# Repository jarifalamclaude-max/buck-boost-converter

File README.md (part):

# SafeBuck-80 — 80 W protected buck-boost (LT8390 + LM74930)

**Banglay:** QS-1212CCBD (80 W automatic buck-boost) er moton ekta module (72 × 54 mm — QS-1212CCBD theke 7 × 6 mm boro, thanda thakar jonno), kintu
**4-switch synchronous buck-boost** (LT8390) diye — efficiency 93–97 % — ar **"smoke-tester" protection** shoho:
input ba output e vhul connection dile board purbe na, shudhu **red LED** jolbe. Puro design KiCad 7 e,
JLCPCB te sorasori order korar file shoho.

**English:** A 72 × 54 mm, 80 W, CV + CC buck-boost module, a little larger than the QS-1212CCBD (65 × 48 mm) for cooling. It uses a 4-switch
synchronous controller (LT8390) and full wrong-wiring protection: reversed input, over-voltage, under-voltage,
output short and a reversed battery on the output. Every one of these only lights a red LED.

| | |
|---|---|
| Input | 9–36 V (starts at 8.2 V, stops below 7.5 V), survives −60 V reversed and up to +60 V DC (cut-off above ~43 V, back on below ~39 V) |
| Output | 1.6–36 V (CV, 25-turn pot; the pot reaches ~39 V) and 0.94–8.33 A (CC, 25-turn pot), max 80 W |
| Topology | 4-switch synchronous buck-boost, 300 kHz ±15 % spread spectrum, peak-current mode |
| Efficiency (calculated) | 96.2–96.9 % (24 → 14.4 V, 80 W) · 93.4–94.8 % (9 → 35 V, 80 W) · 94.7–95.5 % (12 → 12 V) |
| Protection | reverse input to −60 V, OV cut-off ~43 V, UV 7.5 V, inrush limit, input short while running (Q1 gate clamp), output short (CC + 62.5 A instant trip), reversed battery on output (Q7 opens in 1–6 µs), battery above the CV setting (FB clamp), inductive loads (VOUT clamp diode), thermal foldback (PTC), last-resort fuses on both sides |
| Indicators | green = ON, red IN = input reversed / OV / UV, red OUT = battery reversed on the output |
| PCB | 72 × 54 mm (parts in a 65 × 48 mm area, the rest is GND copper for cooling), 2 layers, **2 oz copper**, 1.6 mm, all SMD on top (4 THT parts: 2 terminals, 2 pots), M3 holes in 3 corners |
| Board art | BRACU **Duburi** logo and "Designed by Jarif Alam" on the bottom silkscreen |

| Top (power stage + parts) | Bottom (GND plane, mirrored) |
|---|---|
|  |  |

> **Status / caveat:** the design is checked by calculation (`calc/design.py`: 57 checks, 56 pass, the one "fail" is the
> "bare-board rise above 45 °C at 80 W" note, now +46 °C), by netlist ↔ schematic ↔ PCB consistency checks (`hardware/verify.py`: all pass), by KiCad DRC
> (fully routed: 0 unconnected, 0 clearance, 0 dangling; the only DRC warnings are silkscreen overlaps and library-path notes) and by
> two rounds of independent review (the second round's 8 major findings are fixed or listed under Limitations). **It has not been built and measured yet.** Build one, follow the first-power-up steps in the build guide,
> and check the loop compensation with a load step before trusting it at 80 W.

---

## Documents (shuru korun ekhan theke)

| File | Ki ache |
|---|---|
| [`kicad/`](kicad/) | **KiCad project — open `kicad/SafeBuck-80.kicad_pro`** (schematic + routed PCB + project libraries). `kicad/SafeBuck-80_KiCad.zip` = same files in one download |
| [`docs/SafeBuck-80_Build_Guide.pdf`](docs/SafeBuck-80_Build_Guide.pdf) | **Noob-der jonno**: JLCPCB order step by step, first power-up, CV/CC set, protection test, troubleshooting |
| [`docs/SafeBuck-80_How_It_Works.pdf`](docs/SafeBuck-80_How_It_Works.pdf) | **Sohoj bhashay**: buck/boost kivabe kaj kore (chobi soho), component chena, board map + all 113 parts (ki kaj kore, value keno, na thakle ki hoto), fault table, design process. Source: `docs/make_how_it_works.py` |
| [`docs/SafeBuck-80_Component_Guide.pdf`](docs/SafeBuck-80_Component_Guide.pdf) | **Kon component keno**: every part's role, why it was chosen, full BOM with LCSC numbers |
| [`docs/SafeBuck-80_Schematic.pdf`](docs/SafeBuck-80_Schematic.pdf) | Full schematic (exported from KiCad) |
| [`docs/current_flow/index.html`](docs/current_flow/index.html) | **Current flow page**: 3D board, step-by-step current path (buck, boost, control, input ulta, output-e battery ulta, short), threshold-set-kora part-gulo formula shoho, shob part-er table. Folder download kore browser-e kholo (ba web server diye) |
| [`docs/layout-rules.md`](docs/layout-rules.md) | PCB layout rules used (hot loops, Kelvin sense, ground, thermal) |
| [`jlcpcb/ORDER_NOTES.md`](jlcpcb/ORDER_NOTES.md) | What to upload and which settings to pick at JLCPCB |

## JLCPCB te order (short version)

1. `jlcpcb/SafeBuck-80_gerbers.zip` upload. Settings: **2 layers, 1.6 mm, 2 oz outer copper**.
2. Turn on PCB Assembly (Standard, top side), then upload `jlcpcb/SafeBuck-80_BOM.csv` + `jlcpcb/SafeBuck-80_CPL.csv`.
3. Check the placement preview (pin-1 of U1/U2, FETs, diodes, LEDs, C11/C18 polarity) and order.
   Details are in [`jlcpcb/ORDER_NOTES.md`](jlcpcb/ORDER_NOTES.md).

## File chart — protita file ki kaj kore

| Path | Kaj (what it does) |
|---|---|
| `hardware/netlist.py` | **Single source of truth.** Every part: ref, value, footprint, MPN, LCSC number, role and pad → net map. Everything below is generated from this file |
| `hardware/placement.py` | Position/rotation of every part on the 72 × 54 mm board (hot-loop layout explained in the header) |
| `hardware/build_pcb.py` | Builds the custom LT8390 footprint, places all footprints, assigns nets, draws the outline, runs DRC → `kicad/SafeBuck-80_placed.kicad_pcb` |
| `hardware/route.py` | Power copper zones (union of rectangles, checked against foreign pads) → Specctra DSN (zones as fixed wires, net-tie keepouts) → Freerouting → imports the session → hand fan-out stubs at U2 → completion router → GND pours, stitching vias, GND pocket merge vias and hookups, dead-end cleanup, DRC → `kicad/SafeBuck-80.kicad_pcb` |
| `hardware/complete_routes.py` | Two-layer grid A* router (0.05 mm grid, 0.2 mm track, 0.205 mm gap) that finishes the connections Freerouting leaves open: rip-up with rollback, Kelvin net-tie entry, via keep-back at fine-pitch pins, string-pulled tracks |
| `hardware/make_schematic.py` | Generates the KiCad schematic `kicad/SafeBuck-80.kicad_sch` + project symbol library `SafeBuck.kicad_sym`; symbol UUIDs match the footprints |
| `hardware/make_jlcpcb.py` | Makes the JLCPCB package (Gerber + drill zip, BOM, CPL) |
| `hardware/make_logo.py` | Turns a logo image (`docs/img/duburi_logo.png`) into a silkscreen footprint for the board's bottom side; without an image it draws a "DUBURI" text badge |
| `hardware/verify.py` | One-command check: netlist ↔ schematic ↔ PCB, footprint links, DRC summary |
| `hardware/check_place.sh` | Quick placement check: build, list courtyard overlaps, SVG preview |
| `hardware/routing/SafeBuck-80_freerouting.ses` | The Freerouting session the routed board was built from (input of `route.py complete`) |
| `kicad/` | Copy of the KiCad project for opening/downloading (made by `make_jlcpcb.py`), plus a zip |
| `hardware/kicad/SafeBuck-80.kicad_pro` | KiCad project as generated by the scripts (same files as `kicad/`) |
| `hardware/kicad/SafeBuck-80.kicad_sch` | Schematic (label style: every pin has a net label) |
| `hardware/kicad/SafeBuck-80.kicad_pcb` | Routed 2-layer PCB |
| `hardware/kicad/SafeBuck.kicad_sym`, `SafeBuck.pretty/` | Project libraries: LT8390, LM74930, SOT-23 diode symbols; LT8390 FE28 footprint with 10 thermal vias |
| `hardware/kicad/sym-lib-table`, `fp-lib-table` | Point KiCad at the project libraries (loaded automatically) |
| `hardware/kicad/drc_routed.rpt` | KiCad DRC report of the routed board |
| `calc/design.py` | Every design equation from the datasheets: inductor, RSENSE, slope compensation, losses, ripple, UVLO/OV, inrush, LEDs, thermal, fault simulation of a reversed battery hit → `report.txt`, `results.json` |
| `calc/report.txt` | Human-readable result of all 57 checks |
| `docs/make_docs.py`, `docs/print_pdf.js`, `docs/src/*.html` | Build the PDF guides (edit the HTML, run the script) |
| `jlcpcb/` | Files to upload to JLCPCB |

Regenerate everything (Ubuntu with KiCad 7, Java, Node + Playwright):

```bash
cd hardware && python3 make_logo.py && /usr/bin/python3 build_pcb.py && /usr/bin/python3 route.py complete routing/SafeBuck-80_freerouting.ses && python3 make_schematic.py && /usr/bin/python3 verify.py && python3 make_jlcpcb.py && cd .. && python3 docs/make_docs.py
```

`routing/SafeBuck-80_freerouting.ses` is the Freerouting session this board was made from. `route.py route` runs
Freerouting from scratch instead; its result changes from run to run, so the completion step can end differently.

## Block diagram

```
J1 VIN+ ─ F1 15A ─┬─ D1 TVS        ┌──────── LT8390 4-switch buck-boost ────────┐
                  │                │  Q3 ┐            R15 3mΩ        ┌ Q6        │
                  └─ Q1 ─┬─ Q2 ──── VIN_P ─┤ SW1 ─[RSENSE]─ L1 10µH ─ SW2 ├─ VOUT_C ─ R31 12mΩ ─ F2 10A ─ J2 OUT+
             (HGATE)  CSRC (DGATE) │  Q4 ┘   (peak current)          └ Q5        │     (CC sense)
                     LM74930       └─────────────────────────────────────────────┘
             reverse/OV/UV, FLT→red IN                                    J2 OUT− ─ Q7 (100 V) ─ GND
                                                                 trips: Q9 (I>83 A), Q11 (OUT+<−1.85 V), hold: Q10, red OUT
```

## Fault matrix (vhul connection hole ki hoy)

| Wrong connection | What protects | Result |
|---|---|---|
| Input reversed (up to −60 V) | LM74930 + Q2 block, D1 is bidirectional | red IN LED, no current, nothing hot |
| Input 43–60 V DC | LM74930 OV opens Q1 (back on below 39.4 V; worst case ≥ 37.4 V, so a 36 V supply always restarts) | red IN LED, output off |
| Input shorted while running | D17 (15 V zener) clamps Q1's gate-source; Q2 blocks reverse current | output off, no damage |
| Input spike (hot-plug, cable inductance) | D1 SMBJ60CA, R1/C1 input RC damper, C11 ESR damping | clamped |
| Input below 7.5 V | LM74930 UV + LT8390 EN/UVLO | output off, red IN LED |
| Output short circuit | LT8390 CC limit (keep-running) + 62.5 A instant ISOC | runs at the CC current, recovers when the short is removed |
| Battery reversed on the output (≤ 35 V), any CV setting | Q9 (current > 83 A) or Q11 (OUT+ < −1.85 V) turns Q7 off within 1–6 µs, Q10 holds it off; D15 keeps VOUT_C above about −1.5 V | red OUT LED, peak 52–184 A for a few µs, Q7 avalanche ≤ 19 mJ (rated 274 mJ) |
| Battery (correct polarity) above the CV setting, e.g. 36 V battery at CV 1.6 V | R46 + D14 hold the FB pin below 5.4 V (6 V abs max); LT8390 stops switching (FB over-voltage) | no damage; the battery is not discharged when VIN is off |
| Inductive load (motor, solenoid) when the converter stops | D15 Schottky takes the freewheel current (OUT+ ≈ −1 V, Q11 trips only below −1.85 V) | no false trip, no avalanche |
| Battery on the output, correct polarity, input off | Q7 off without VIN | no drain (µA) |
| Overheating | PTC TH1 pulls CTRL down | current folds back at about 105 °C, stops at about 130 °C, auto-restarts |
| A MOSFET fails short | F1 / F2 | fuse opens (last resort only) |

**Never connect OUT− to VIN− outside the board (no common ground).** OUT− is switched by Q7. With a common ground the
converter still works, but (1) a battery reversed on the output is no longer blocked (F2 has to blow), and (2) if the
input is then also reversed, the supply is shorted through Q7's body diode. Use a floating load / separate supply,
which is how a bench "smoke tester" is normally wired.

## KiCad libraries used

| Library | Used for |
|---|---|
| `Device` (KiCad 7 standard) | R, C, C_Polarized, L, D, D_TVS, LED, Fuse, R_Potentiometer, Thermistor_PTC, Q_NPN_BEC, Q_PNP_BEC, NetTie_2 symbols |
| `Transistor_FET` | CSD18532Q5B, CSD19532Q5B symbols (TDSON-8 pinout: 1–3 S, 4 G, 5 D) |
| `Connector`, `Mechanical` | Screw_Terminal_01x02, TestPoint, MountingHole |
| `SafeBuck` (this project, `SafeBuck.kicad_sym`) | LT8390, LM74930, D_SOT23 (BAS21), DZ_SOT23 (BZX84) |
| Footprints: `Resistor_SMD`, `Capacitor_SMD`, `Diode_SMD`, `LED_SMD`, `Package_TO_SOT_SMD` (SOT-23, TDSON-8-1), `Package_DFN_QFN` (HVQFN-24 4×4), `Inductor_SMD` (L_Coilcraft_XAL1510-103), `Fuse` (Littelfuse NANO2 451/453), `Potentiometer_THT` (Bourns 3296W), `TerminalBlock_Phoenix` (MKDS 1,5/2-5,08), `TestPoint`, `MountingHole`, `NetTie` | Standard KiCad 7 footprints |
| `SafeBuck.pretty` (this project) | `LT8390_FE28_EB_TSSOP-28_EP4.75x2.74mm`: ADI FE28 (EB) land pattern with 2 × 5 thermal vias |

## Datasheets and sources I read

**Chosen parts**
- LT8390 (Analog Devices): https://www.analog.com/media/en/technical-documentation/data-sheets/LT8390.pdf
  (the copy I worked from was the public Chinese version hosted by LCSC: https://atta.szlcsc.com/upload/public/pdf/source/20221018/54D796C872281B2AD115D8A08B7AE0F6.pdf)
- LM74930-Q1 (TI): https://www.ti.com/lit/ds/symlink/lm74930-q1.pdf
- CSD18532Q5B (TI): https://www.ti.com/lit/ds/symlink/csd18532q5b.pdf
- CSD19532Q5B (TI): https://www.ti.com/lit/ds/symlink/csd19532q5b.pdf
- Coilcraft XAL1510: https://www.coilcraft.com/getmedia/cd1cef27-13f0-4568-8894-f7311475209b/xal1510.pdf
- Panasonic hybrid polymer ZA/ZC series (C18): https://na.industrial.panasonic.com/products/capacitors/polymer-capacitors/lineup/polymer-hybrid-aluminum-electrolytic-capacitor/series/79
- Panasonic EEE-FK1J101P (C11): https://www.digikey.ca/en/products/detail/panasonic-industry/EEE-FK1J101P/766195
- Murata GRM32EC72A106KE05L (10 µF 100 V): https://www.digikey.ca/en/products/detail/murata-electronics/GRM32EC72A106KE05L/7319245
- Murata PRF18 PTC: https://pim.murata.com/en-us/pim/details/?partNum=PRF18BC471QB5RB and spec https://pim.murata.com/asset/pim4/ptcForTemperatureSensor/SPEC_PRF18_471_PDF_PTCFORTEMPERATURESENSOR
- Littelfuse NANO² 451/453 fuses: https://www.littelfuse.com/products/fuses/surface-mount-fuses/nano-2-fuses/451_453.aspx
- Littelfuse SMBJ TVS: https://www.littelfuse.com/products/tvs-diodes/surface-mount/smbj.aspx

**Compared and rejected (why, in the component guide)**
- TI LM5176 https://www.ti.com/lit/ds/symlink/lm5176.pdf · LM5177 https://www.ti.com/lit/ds/symlink/lm5177.pdf (other buck-boost controllers)
- TI LM74502-Q1 https://www.ti.com/lit/ds/symlink/lm74502-q1.pdf · TPS1211-Q1 https://www.ti.com/lit/ds/symlink/tps1211-q1.pdf · LM74700-Q1 https://www.ti.com/lit/ds/symlink/lm74700-q1.pdf (other front-ends)
- TI CSD18540Q5B https://www.ti.com/lit/ds/symlink/csd18540q5b.pdf (best FET, but only 2 in stock at JLCPCB) · CSD18531Q5A https://www.ti.com/lit/ds/symlink/csd18531q5a.pdf · CSD18543Q3A https://www.ti.com/lit/ds/symlink/csd18543q3a.pdf · CSD19533Q5A https://www.ti.com/lit/ds/symlink/csd19533q5a.pdf
- Vishay SiR5607DP P-MOSFET https://www.vishay.com/docs/62247/sir5607dp.pdf (first output-switch idea; rejected: it runs in linear mode in a dead short)
- Bourns SRP1770TA https://www.bourns.com/docs/Product-Datasheets/SRP1770TA.pdf (first inductor choice; out of stock at JLCPCB)

**The original module**
- RoboticsBD QS-1212CCBD page: https://store.roboticsbd.com/power-module-adapter/4598-qs-1212ccbd-80w-automatic-buck-boost-power-supply-module-robotics-bangladesh.html
- QS-1224CBD (sibling) test/teardown with reverse-engineered schematic (UC3843A): https://chinese-electronics-products-tested.blogspot.com/p/qs-1224cbd-dc-dc-converter-tested.html
- Cirkit Designer QS-1212CCBD page: https://docs.cirkitdesigner.com/component/20a9b9bf-1da5-4816-b42f-8383cbccc88f/mdulo-qs-1212ccbd-80w-buck-boost
- JLCPCB parts library (stock and LCSC numbers, checked 2026-11-18): https://jlcpcb.com/parts

## Limitations (shotti kotha)

- **Not built yet.** The numbers come from datasheet equations and a simple fault model, not from measurements.
- **Loop compensation** (R22 10 k, C29 22 nF, C30 100 pF) is a calculated start value. Check it with a load step
  (for example 1 A → 6 A) on an oscilloscope, or in LTspice (the LT8390 model is free from ADI).
- **Switching loss** is an estimate (two models, about 1 % apart); real efficiency can be 1–2 % lower.
- **JLCPCB rotations**: the CPL applies the usual KiCad → JLC corrections (SOT-23, QFN, TSSOP, CP_Elec). Always check the
  placement preview.
- **Heat at 80 W:** the larger board (72 × 54 mm) brings the worst-case rise down from about +57 °C to about +46 °C above
  ambient (MOSFETs about 97 °C at 40 °C ambient, well below their 150 °C limit). At room temperature it runs 80 W without a
  heatsink. In a closed box, above about 40 °C ambient, or for hours at 80 W, screw a 40 × 40 mm heatsink under the board
  (then about +26 °C).
- The reversed-battery protection assumes a battery of 35 V or less (Q7 blocks VOUT + battery, up to about 75 V).
- **No input power limit.** The CC limit (up to 8.33 A) and the inductor peak limit allow more than 80 W at high output voltage
  (for example 36 V × 8 A). Set the CC pot so that VOUT × ICC ≤ 80 W. If you overload it anyway, the PTC folds the current
  back at about 105 °C and F1 (15 A) is the last resort.
- **Common ground** between input and output defeats the output reverse protection (see the warning above).
- In the highest-voltage reversed-battery cases (for example a 35 V battery at CV 35 V) Q7 turns off at up to ~180 A, above
  the 74 A that TI's avalanche graph is drawn to. The energy is small (≤ 19 mJ of a 274 mJ rating) and lasts < 2 µs, but it
  is outside the tested area of the datasheet.
- The LM74930 allows at most 85 V between its C and A pins. If the input is reversed to −60 V within seconds of running at
  more than about 26 V (input caps still charged), that limit is exceeded. Wait a few seconds, or keep the reverse voltage
  at or below −48 V.
- The NANO² fuses (F1, F2) break at most 50 A. They are a last resort against a failed MOSFET, not against a battery
  short.
- C18 carries about 2.2 A rms at the 9 V → 35 V, 80 W corner (rated 1.8 A at 105 °C, about 2.5 A at 85 °C). For long use at
  that corner, keep the board cool or stay at or below 65 W.
- **Ground around U1:** on two layers the signal tracks around the LT8390 cut the bottom GND plane into pockets. They are
  joined to the main GND by extra vias, and U1's exposed pad also connects through its 10 thermal vias and a top-layer
  link to pin 10, but this is not a solid plane under the IC. U1 loses up to about 1 W at 36 V in (INTVCC regulator).
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
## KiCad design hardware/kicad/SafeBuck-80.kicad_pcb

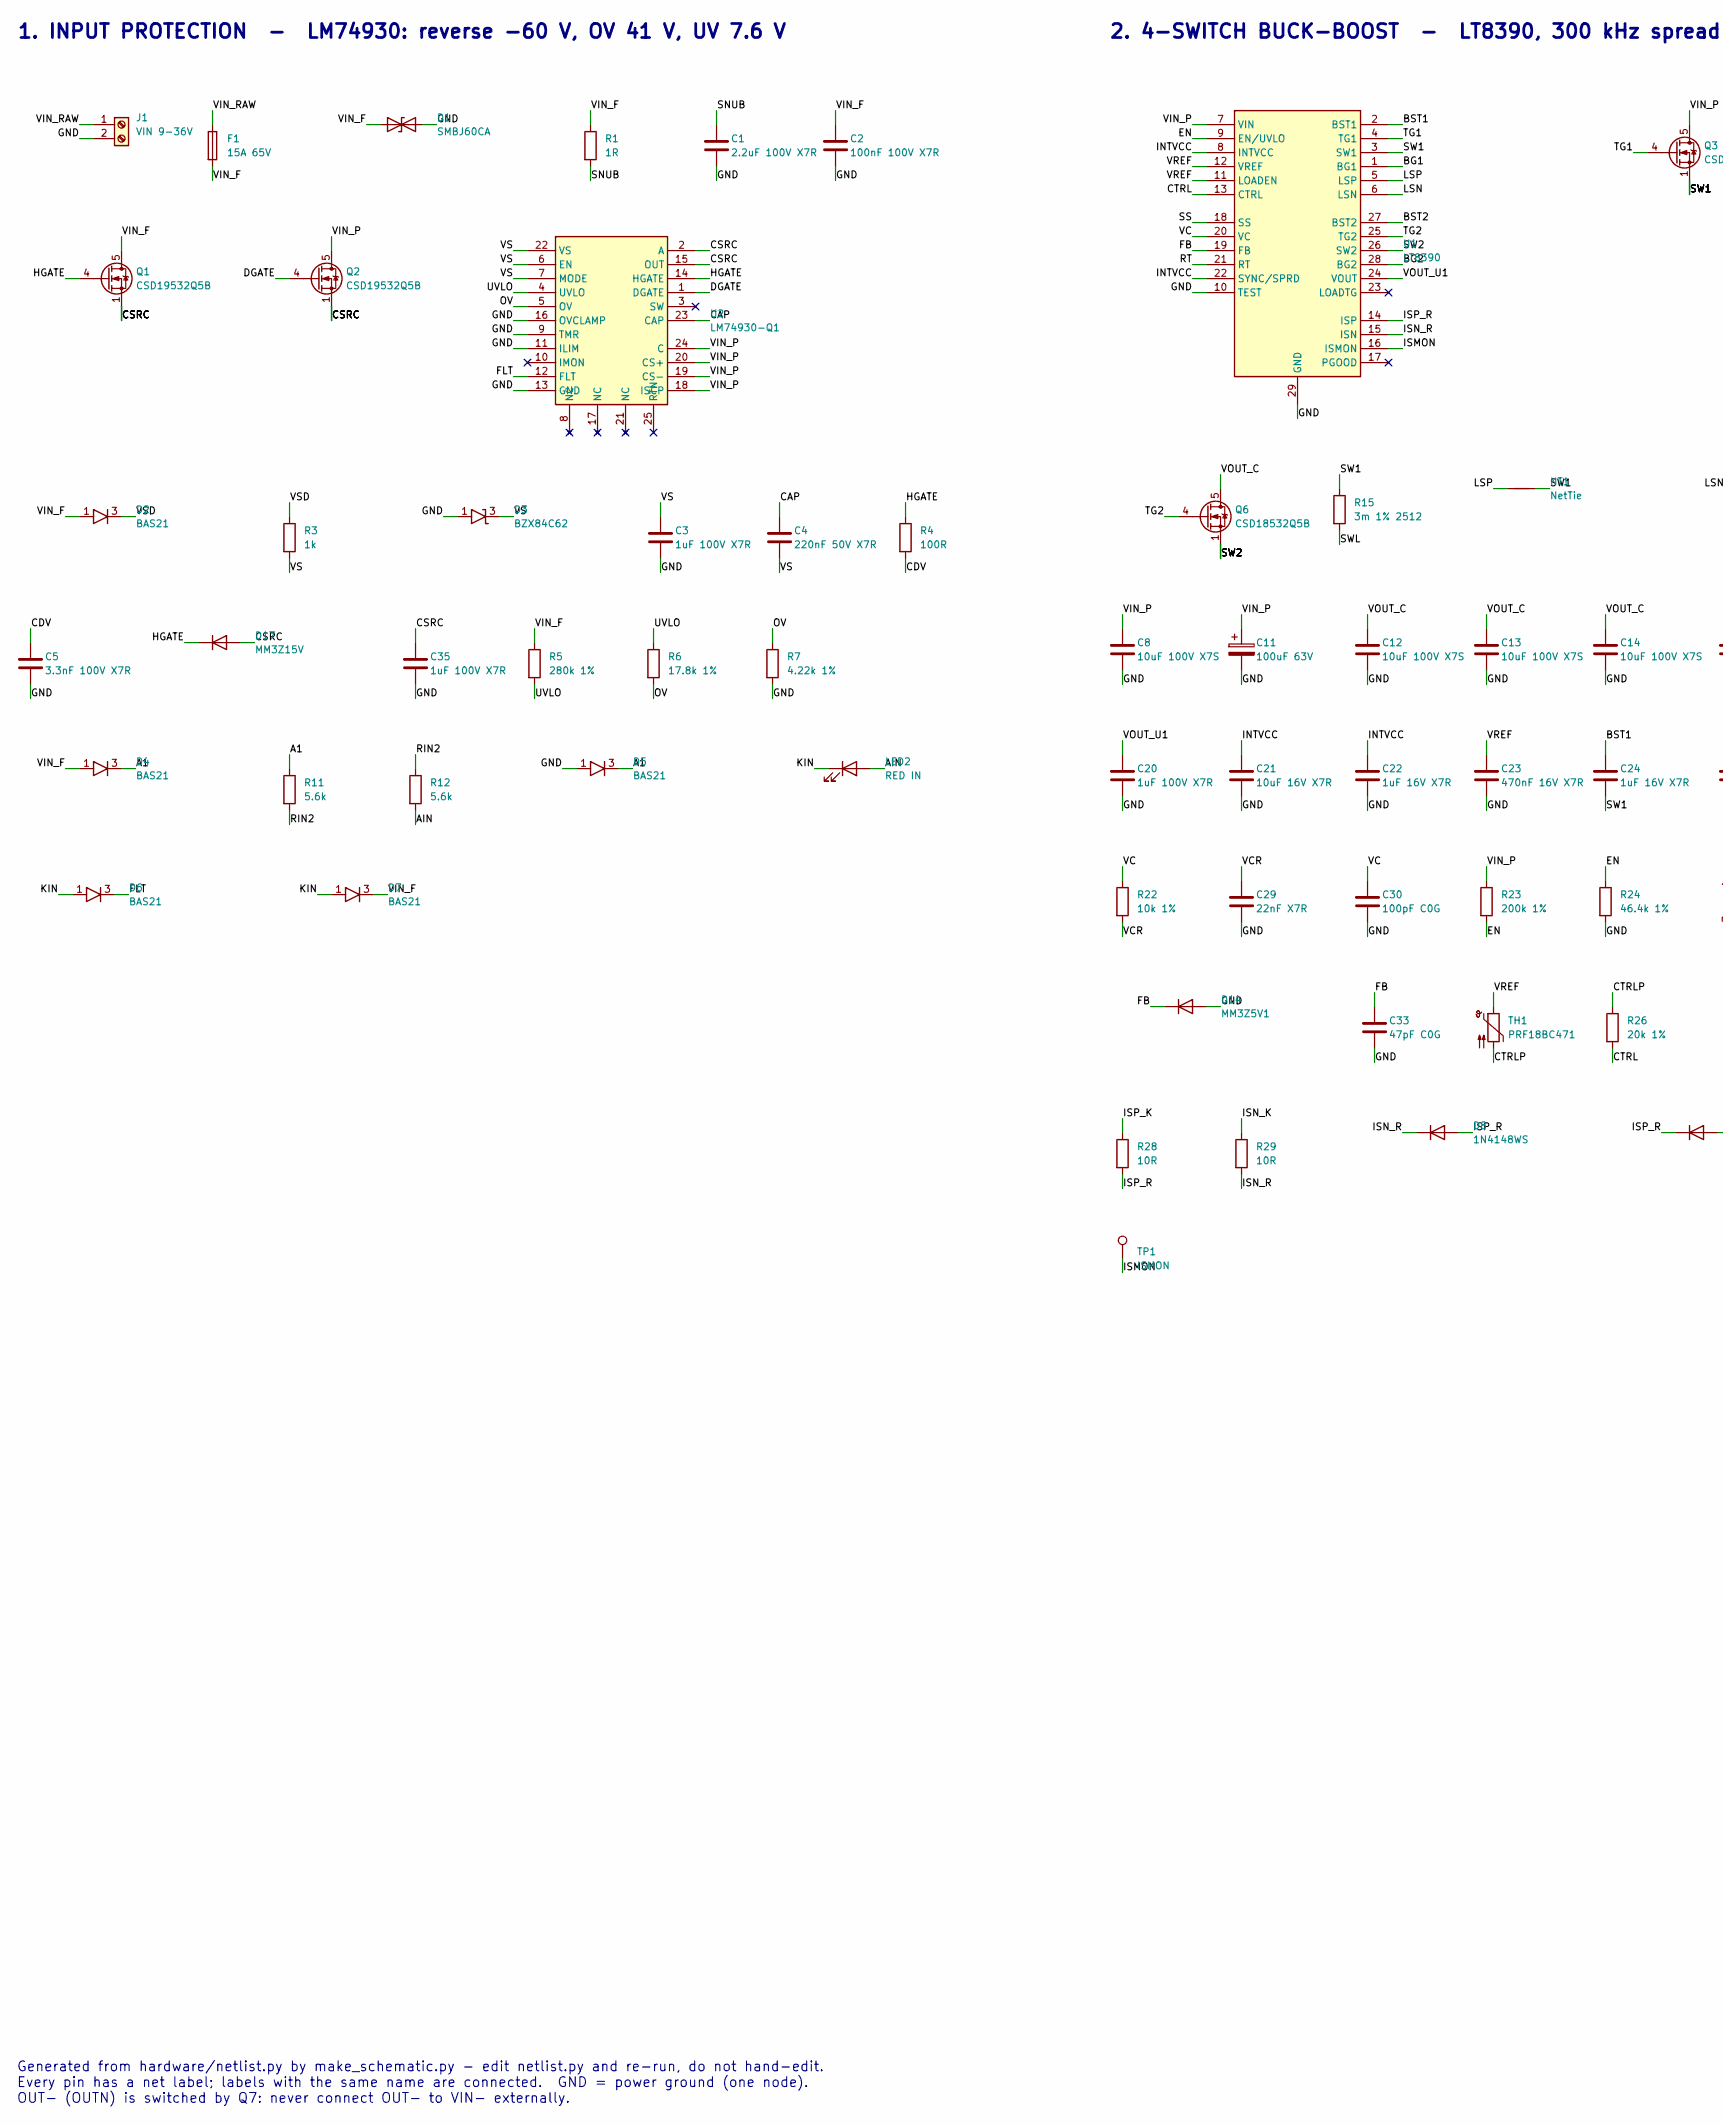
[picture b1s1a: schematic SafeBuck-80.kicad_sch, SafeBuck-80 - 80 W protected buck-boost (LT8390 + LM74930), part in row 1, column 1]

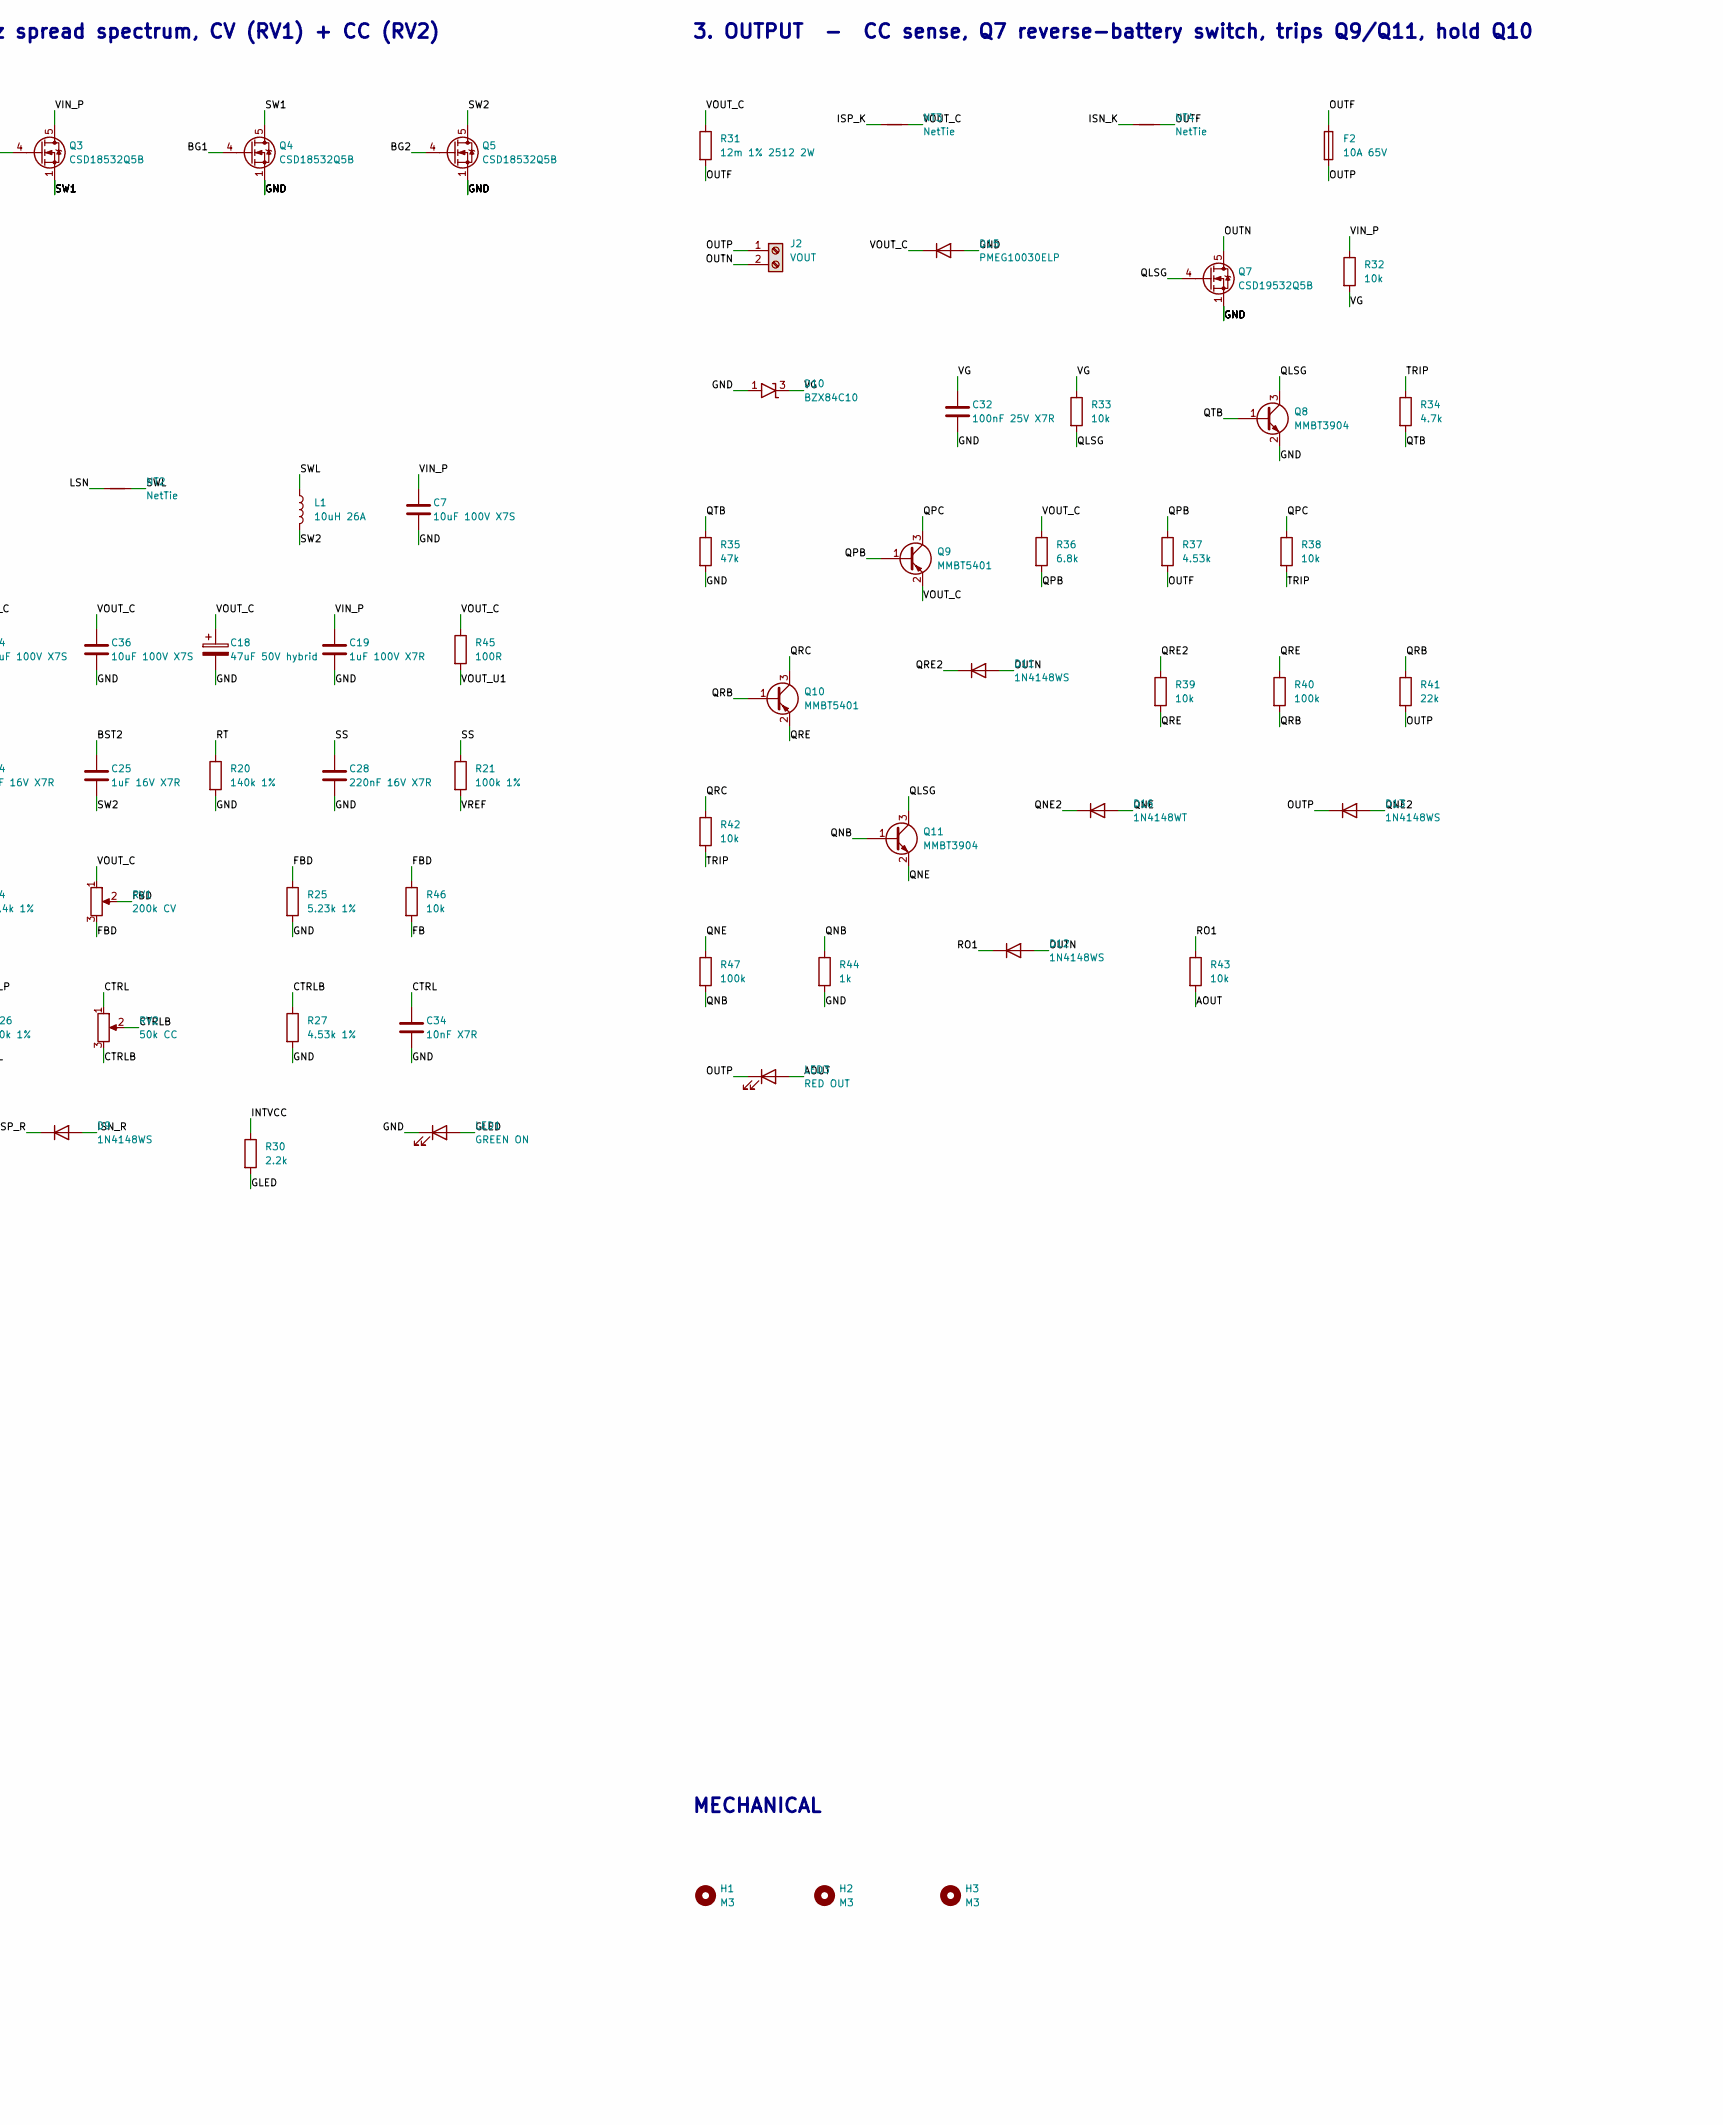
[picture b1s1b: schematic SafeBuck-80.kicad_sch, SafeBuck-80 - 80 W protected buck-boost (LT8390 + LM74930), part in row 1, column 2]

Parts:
C1: 2.2uF 100V X7R; C_1210_3225Metric; LCSC C55151
C2: 100nF 100V X7R; C_0603_1608Metric; LCSC C15725
C3, C19, C20, C35: 1uF 100V X7R; C_0805_2012Metric; LCSC C105952
C4: 220nF 50V X7R; C_0603_1608Metric; LCSC C64705
C5: 3.3nF 100V X7R; C_0603_1608Metric; LCSC C113805
C7, C8, C12, C13, C14, C36: 10uF 100V X7S; C_1210_3225Metric; MPN GRM32EC72A106KE05L; LCSC C576517
C11: 100uF 63V; CP_Elec_10x10; MPN EEE-FK1J101P; LCSC C128460
C18: 47uF 50V hybrid; CP_Elec_8x10; MPN EEHZA1H470P; LCSC C454653
C21: 10uF 16V X7R; C_0805_2012Metric; LCSC C95841
C22, C24, C25: 1uF 16V X7R; C_0603_1608Metric; LCSC C29936
C23: 470nF 16V X7R; C_0603_1608Metric; LCSC C1623
C28: 220nF 16V X7R; C_0603_1608Metric; LCSC C21120
C29: 22nF X7R; C_0603_1608Metric; LCSC C21122
C30: 100pF C0G; C_0603_1608Metric; LCSC C14858
C32: 100nF 25V X7R; C_0603_1608Metric; LCSC C14663
C33: 47pF C0G; C_0603_1608Metric; LCSC C1671
C34: 10nF X7R; C_0603_1608Metric; LCSC C57112
D1: SMBJ60CA; D_SMB; MPN SMBJ60CA; LCSC C115824
D2, D4, D5, D6, D7: BAS21; SOT-23; MPN BAS21; LCSC C79596
D3: BZX84C62; SOT-23; MPN BZX84C62; LCSC C238878
D8, D9, D11, D12, D13: 1N4148WS; D_SOD-323; MPN 1N4148WS; LCSC C2128
D10: BZX84C10; SOT-23; MPN BZX84C10; LCSC C82476
D14: MM3Z5V1; D_SOD-323; MPN MM3Z5V1T1G; LCSC C75074
D15: PMEG10030ELP; D_SOD-128; MPN PMEG10030ELPX; LCSC C5260346
D16: 1N4148WT; D_SOD-523; MPN 1N4148WT; LCSC C27748
D17: MM3Z15V; D_SOD-323; MPN MM3Z15VT1G; LCSC C603316
F1: 15A 65V; Fuse_Littelfuse-NANO2-451_453; MPN 0451015.MRL; LCSC C44480
F2: 10A 65V; Fuse_Littelfuse-NANO2-451_453; MPN 0451010.MRL; LCSC C44479
H1, H2, H3: M3; MountingHole_3.2mm_M3
J1: VIN 9-36V; TerminalBlock_Phoenix_MKDS-1,5-2-5.08_1x02_P5.08mm_Horizont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; MPN WJ500V-5.08-2P; LCSC C8465
J2: VOUT; TerminalBlock_Phoenix_MKDS-1,5-2-5.08_1x02_P5.08mm_Horizont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; MPN WJ500V-5.08-2P; LCSC C8465
L1: 10uH 26A; L_Coilcraft_XAL1510-103; MPN XAL1510-103MED; LCSC C3911782
LED1: GREEN ON; LED_0805_2012Metric; LCSC C2297
LED2: RED IN; LED_0805_2012Metric; LCSC C84256
LED3: RED OUT; LED_0805_2012Metric; LCSC C84256
NT1, NT2, NT3, NT4: NetTie; NetTie-2_SMD_Pad0.5mm
Q1, Q2, Q7: CSD19532Q5B; TDSON-8-1; MPN CSD19532Q5B; LCSC C473333
Q3, Q4, Q5, Q6: CSD18532Q5B; TDSON-8-1; MPN CSD18532Q5B; LCSC C882766
Q8, Q11: MMBT3904; SOT-23; MPN MMBT3904; LCSC C20526
Q9, Q10: MMBT5401; SOT-23; MPN MMBT5401; LCSC C8326
R1: 1R; R_1206_3216Metric; LCSC C17928
R3: 1k; R_0805_2012Metric; LCSC C17513
R4, R45: 100R; R_0603_1608Metric; LCSC C22775
R5: 280k 1%; R_0805_2012Metric; LCSC C17597
R6: 17.8k 1%; R_0603_1608Metric; LCSC C22821
R7: 4.22k 1%; R_0603_1608Metric; LCSC C23042
R11, R12: 5.6k; R_1206_3216Metric; LCSC C18028
R15: 3m 1% 2512; R_2512_6332Metric; MPN WSL2512R0030FEA (or eq.); LCSC C723728
R20: 140k 1%; R_0603_1608Metric; LCSC C22875
R21: 100k 1%; R_0603_1608Metric; LCSC C25803
R22: 10k 1%; R_0603_1608Metric; LCSC C25804
R23: 200k 1%; R_0805_2012Metric; LCSC C17539
R24: 46.4k 1%; R_0603_1608Metric; LCSC C23059
R25: 5.23k 1%; R_0603_1608Metric; LCSC C23068
R26: 20k 1%; R_0603_1608Metric; LCSC C4184
R27: 4.53k 1%; R_0603_1608Metric; LCSC C25971
R28, R29: 10R; R_0603_1608Metric; LCSC C22859
R30: 2.2k; R_0603_1608Metric; LCSC C4190
R31: 12m 1% 2512 2W; R_2512_6332Metric; MPN WSLP2512R0120FEA (or eq. 2 W); LCSC C19633815
R32, R43: 10k; R_1206_3216Metric; LCSC C17902
R33, R38, R39, R42, R46: 10k; R_0603_1608Metric; LCSC C25804
R34: 4.7k; R_0603_1608Metric; LCSC C23162
R35: 47k; R_0603_1608Metric; LCSC C25819
R36: 6.8k; R_0603_1608Metric; LCSC C23212
R37: 4.53k; R_0603_1608Metric; LCSC C25971
R40: 100k; R_0603_1608Metric; LCSC C25803
R41: 22k; R_0603_1608Metric; LCSC C31850
R44: 1k; R_0603_1608Metric; LCSC C21190
R47: 100k; R_0402_1005Metric; LCSC C25741
RV1: 200k CV; Potentiometer_Bourns_3296W_Vertical; MPN 3296W-1-204; LCSC C58354
RV2: 50k CC; Potentiometer_Bourns_3296W_Vertical; MPN 3296W-1-503; LCSC C83686
TH1: PRF18BC471; R_0603_1608Metric; MPN PRF18BC471QB5RB; LCSC C152572
TP1: ISMON; TestPoint_Pad_D1.5mm
U1: LT8390; LT8390_FE28_EB_TSSOP-28_EP4.75x2.74mm; MPN LT8390EFE#TRPBF; LCSC C673802
U2: LM74930-Q1; HVQFN-24-1EP_4x4mm_P0.5mm_EP2.1x2.1mm; MPN LM74930QRGERQ1; LCSC C22428070

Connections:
A1: D4.3 (K), D5.3 (K), R11.1
AIN: LED2.2 (A), R12.2
AOUT: LED3.2 (A), R43.2
BG1: Q4.4 (G), U1.1 (BG1)
BG2: Q5.4 (G), U1.28 (BG2)
BST1: C24.1, U1.2 (BST1)
BST2: C25.1, U1.27 (BST2)
CAP: C4.1, U2.23 (CAP)
CDV: C5.1, R4.2
CSRC: C35.1, D17.2 (A), Q1.1 (S), Q1.2 (S), Q1.3 (S), Q2.1 (S), Q2.2 (S), Q2.3 (S), U2.2 (A), U2.15 (OUT)
CTRL: C34.1, R26.2, RV2.1, U1.13 (CTRL)
CTRLB: R27.1, RV2.2, RV2.3
CTRLP: R26.1, TH1.2
DGATE: Q2.4 (G), U2.1 (DGATE)
EN: R23.2, R24.1, U1.9 (EN/UVLO)
FB: C33.1, D14.1 (K), R46.2, U1.19 (FB)
FBD: R25.1, R46.1, RV1.2, RV1.3
FLT: D6.3 (K), U2.12 (FLT)
GLED: LED1.2 (A), R30.2
GND: C1.2, C2.2, C3.2, C5.2, C7.2, C8.2, C11.2, C12.2, C13.2, C14.2, C18.2, C19.2, C20.2, C21.2, C22.2, C23.2, C28.2, C29.2, C30.2, C32.2, C33.2, C34.2, C35.2, C36.2, D1.2 (A2), D3.1 (A), D5.1 (A), D10.1 (A), D14.2 (A), D15.2 (A), J1.2, LED1.1 (K), Q4.1 (S), Q4.2 (S), Q4.3 (S), Q5.1 (S), Q5.2 (S), Q5.3 (S), Q7.1 (S), Q7.2 (S), Q7.3 (S), Q8.2 (E), R7.2, R20.2, R24.2, R25.2, R27.2, R35.2, R44.2, U1.10 (TEST), U1.29 (GND), U2.9 (TMR), U2.11 (ILIM), U2.13 (GND), U2.16 (OVCLAMP)
HGATE: D17.1 (K), Q1.4 (G), R4.1, U2.14 (HGATE)
INTVCC: C21.1, C22.1, R30.1, U1.8 (INTVCC), U1.22 (SYNC/SPRD)
ISMON: TP1.1, U1.16 (ISMON)
ISN_K: NT4.1, R29.1
ISN_R: D8.1 (K), D9.2 (A), R29.2, U1.15 (ISN)
ISP_K: NT3.1, R28.1
ISP_R: D8.2 (A), D9.1 (K), R28.2, U1.14 (ISP)
KIN: D6.1 (A), D7.1 (A), LED2.1 (K)
LSN: NT2.1, U1.6 (LSN)
LSP: NT1.1, U1.5 (LSP)
NC_U1_LOADTG: U1.23 (LOADTG)
NC_U1_PGOOD: U1.17 (PGOOD)
NC_U2_8: U2.8 (NC)
NC_U2_17: U2.17 (NC)
NC_U2_21: U2.21 (NC)
NC_U2_IMON: U2.10 (IMON)
OUTF: F2.1, NT4.2, R31.2, R37.2
OUTN: D11.2 (A), D12.2 (A), J2.2, Q7.5 (D)
OUTP: D13.1 (K), F2.2, J2.1, LED3.1 (K), R41.2
OV: R6.2, R7.1, U2.5 (OV)
QLSG: Q7.4 (G), Q8.3 (C), Q11.3 (C), R33.2
QNB: Q11.1 (B), R44.1, R47.2
QNE: D16.2 (A), Q11.2 (E), R47.1
QNE2: D13.2 (A), D16.1 (K)
QPB: Q9.1 (B), R36.2, R37.1
QPC: Q9.3 (C), R38.1
QRB: Q10.1 (B), R40.2, R41.1
QRC: Q10.3 (C), R42.1
QRE: Q10.2 (E), R39.2, R40.1
QRE2: D11.1 (K), R39.1
QTB: Q8.1 (B), R34.2, R35.1
RIN2: R11.2, R12.1
RO1: D12.1 (K), R43.1
RT: R20.1, U1.21 (RT)
RTN: U2.25 (RTN)
SNUB: C1.1, R1.2
SS: C28.1, R21.1, U1.18 (SS)
SW1: C24.2, NT1.2, Q3.1 (S), Q3.2 (S), Q3.3 (S), Q4.5 (D), R15.1, U1.3 (SW1)
SW2: C25.2, L1.2, Q5.5 (D), Q6.1 (S), Q6.2 (S), Q6.3 (S), U1.26 (SW2)
SWL: L1.1, NT2.2, R15.2
TG1: Q3.4 (G), U1.4 (TG1)
TG2: Q6.4 (G), U1.25 (TG2)
TRIP: R34.1, R38.2, R42.2
U2_SW: U2.3 (SW)
UVLO: R5.2, R6.1, U2.4 (UVLO)
VC: C30.1, R22.1, U1.20 (VC)
VCR: C29.1, R22.2
VG: C32.1, D10.3 (K), R32.2, R33.1
VIN_F: C2.1, D1.1 (A1), D2.1 (A), D4.1 (A), D7.3 (K), F1.2, Q1.5 (D), R1.1, R5.1
VIN_P: C7.1, C8.1, C11.1, C19.1, Q2.5 (D), Q3.5 (D), R23.1, R32.1, U1.7 (VIN), U2.18 (ISCP), U2.19 (CS-), U2.20 (CS+), U2.24 (C)
VIN_RAW: F1.1, J1.1
VOUT_C: C12.1, C13.1, C14.1, C18.1, C36.1, D15.1 (K), NT3.2, Q6.5 (D), Q9.2 (E), R31.1, R36.1, R45.1, RV1.1
VOUT_U1: C20.1, R45.2, U1.24 (VOUT)
VREF: C23.1, R21.2, TH1.1, U1.11 (LOADEN), U1.12 (VREF)
VS: C3.1, C4.2, D3.3 (K), R3.2, U2.6 (EN), U2.7 (MODE), U2.22 (VS)
VSD: D2.3 (K), R3.1

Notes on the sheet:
1. INPUT PROTECTION - LM74930: reverse -60 V, OV 41 V, UV 7.6 V
2. 4-SWITCH BUCK-BOOST - LT8390, 300 kHz spread spectrum, CV (RV1) + CC (RV2)
3. OUTPUT - CC sense, Q7 reverse-battery switch, trips Q9/Q11, hold Q10
MECHANICAL
Generated from hardware/netlist.py by make_schematic.py - edit netlist.py and re-run, do not hand-edit. Every pin has a net label; labels with the same name are connected. GND = power ground (one node). OUT- (OUTN) is switched by Q7: never connect OUT- to VIN- externally.

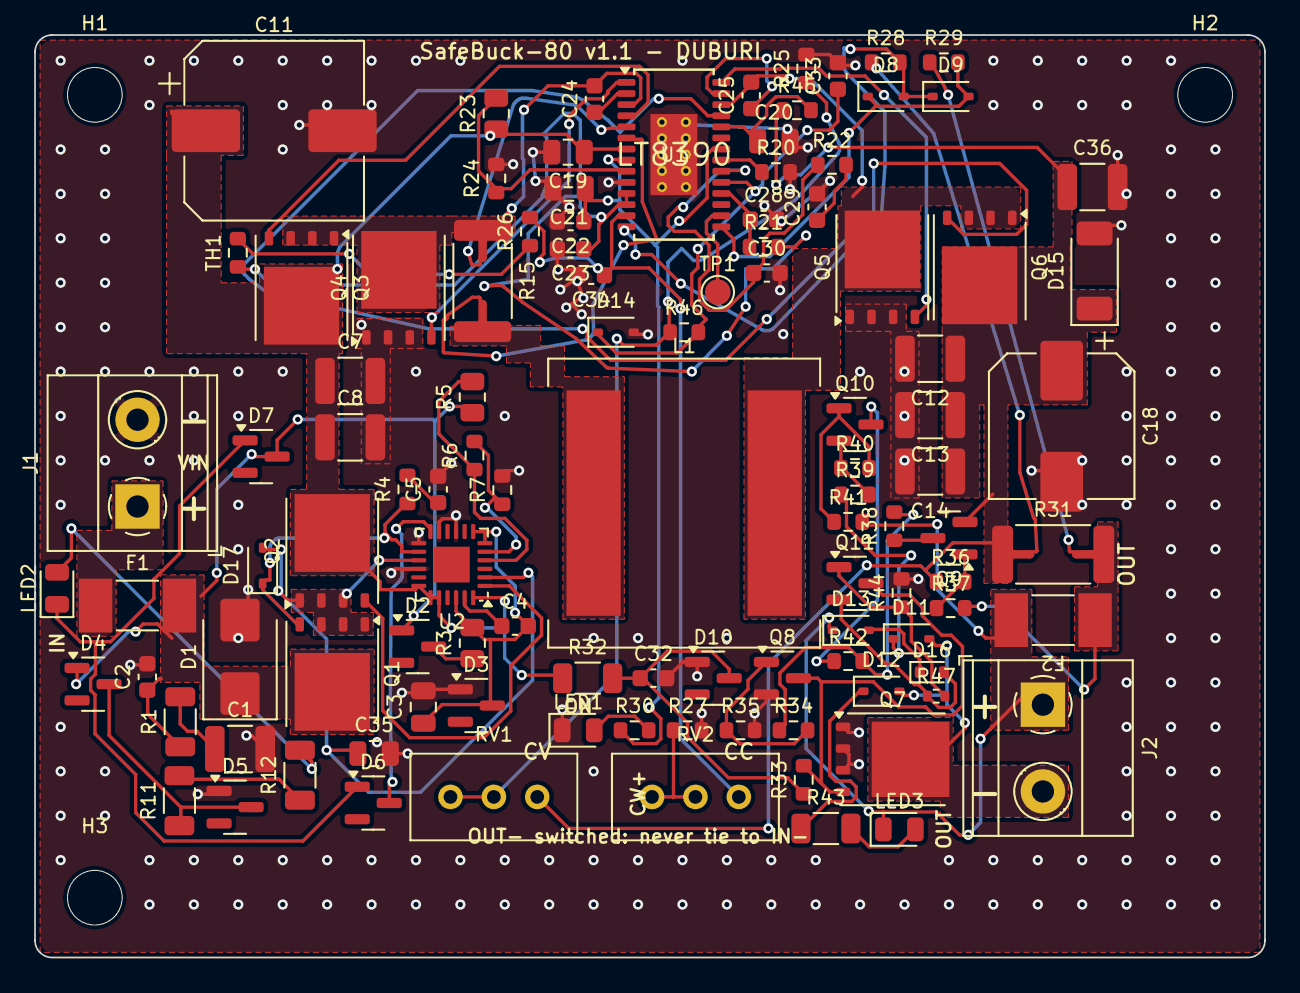
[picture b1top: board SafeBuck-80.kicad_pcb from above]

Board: 2 copper layers, 72.0 x 54.0 mm, 114 parts (1 on the bottom side), 68 nets.

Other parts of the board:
LOGO1: Logo_Duburi

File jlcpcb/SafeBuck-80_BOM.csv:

Comment,Designator,Footprint,LCSC Part #
2.2uF 100V X7R,C1,C_1210_3225Metric,C55151
100nF 100V X7R,C2,C_0603_1608Metric,C15725
1uF 100V X7R,"C3,C19,C20,C35",C_0805_2012Metric,C105952
220nF 50V X7R,C4,C_0603_1608Metric,C64705
3.3nF 100V X7R,C5,C_0603_1608Metric,C113805
10uF 100V X7S,"C7,C8,C12,C13,C14,C36",C_1210_3225Metric,C576517
100uF 63V,C11,CP_Elec_10x10,C128460
47uF 50V hybrid,C18,CP_Elec_8x10,C454653
10uF 16V X7R,C21,C_0805_2012Metric,C95841
1uF 16V X7R,"C22,C24,C25",C_0603_1608Metric,C29936
470nF 16V X7R,C23,C_0603_1608Metric,C1623
220nF 16V X7R,C28,C_0603_1608Metric,C21120
22nF X7R,C29,C_0603_1608Metric,C21122
100pF C0G,C30,C_0603_1608Metric,C14858
100nF 25V X7R,C32,C_0603_1608Metric,C14663
47pF C0G,C33,C_0603_1608Metric,C1671
10nF X7R,C34,C_0603_1608Metric,C57112
SMBJ60CA,D1,D_SMB,C115824
BAS21,"D2,D4,D5,D6,D7",SOT-23,C79596
BZX84C62,D3,SOT-23,C238878
1N4148WS,"D8,D9,D11,D12,D13",D_SOD-323,C2128
BZX84C10,D10,SOT-23,C82476
MM3Z5V1,D14,D_SOD-323,C75074
PMEG10030ELP,D15,D_SOD-128,C5260346
1N4148WT,D16,D_SOD-523,C27748
MM3Z15V,D17,D_SOD-323,C603316
15A 65V,F1,Fuse_Littelfuse-NANO2-451_453,C44480
10A 65V,F2,Fuse_Littelfuse-NANO2-451_453,C44479
VIN 9-36V,J1,"TerminalBlock_Phoenix_MKDS-1,5-2-5.08_1x02_P5.08mm_Horizontal",C8465
VOUT,J2,"TerminalBlock_Phoenix_MKDS-1,5-2-5.08_1x02_P5.08mm_Horizontal",C8465
10uH 26A,L1,L_Coilcraft_XAL1510-103,C3911782
GREEN ON,LED1,LED_0805_2012Metric,C2297
RED  IN,LED2,LED_0805_2012Metric,C84256
RED OUT,LED3,LED_0805_2012Metric,C84256
CSD19532Q5B,"Q1,Q2,Q7",TDSON-8-1,C473333
CSD18532Q5B,"Q3,Q4,Q5,Q6",TDSON-8-1,C882766
MMBT3904,"Q8,Q11",SOT-23,C20526
MMBT5401,"Q9,Q10",SOT-23,C8326
1R,R1,R_1206_3216Metric,C17928
1k,R3,R_0805_2012Metric,C17513
100R,"R4,R45",R_0603_1608Metric,C22775
280k 1%,R5,R_0805_2012Metric,C17597
17.8k 1%,R6,R_0603_1608Metric,C22821
4.22k 1%,R7,R_0603_1608Metric,C23042
5.6k,"R11,R12",R_1206_3216Metric,C18028
3m 1% 2512,R15,R_2512_6332Metric,C723728
140k 1%,R20,R_0603_1608Metric,C22875
100k 1%,R21,R_0603_1608Metric,C25803
10k 1%,R22,R_0603_1608Metric,C25804
200k 1%,R23,R_0805_2012Metric,C17539
46.4k 1%,R24,R_0603_1608Metric,C23059
5.23k 1%,R25,R_0603_1608Metric,C23068
20k 1%,R26,R_0603_1608Metric,C4184
4.53k 1%,R27,R_0603_1608Metric,C25971
10R,"R28,R29",R_0603_1608Metric,C22859
2.2k,R30,R_0603_1608Metric,C4190
12m 1% 2512 2W,R31,R_2512_6332Metric,C19633815
10k,"R32,R43",R_1206_3216Metric,C17902
10k,"R33,R38,R39,R42,R46",R_0603_1608Metric,C25804
4.7k,R34,R_0603_1608Metric,C23162
47k,R35,R_0603_1608Metric,C25819
6.8k,R36,R_0603_1608Metric,C23212
4.53k,R37,R_0603_1608Metric,C25971
100k,R40,R_0603_1608Metric,C25803
22k,R41,R_0603_1608Metric,C31850
1k,R44,R_0603_1608Metric,C21190
100k,R47,R_0402_1005Metric,C25741
200k CV,RV1,Potentiometer_Bourns_3296W_Vertical,C58354
50k CC,RV2,Potentiometer_Bourns_3296W_Vertical,C83686
PRF18BC471,TH1,R_0603_1608Metric,C152572
LT8390,U1,LT8390_FE28_EB_TSSOP-28_EP4.75x2.74mm,C673802
LM74930-Q1,U2,HVQFN-24-1EP_4x4mm_P0.5mm_EP2.1x2.1mm,C22428070

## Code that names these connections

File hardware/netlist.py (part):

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part('J1', 'VIN 9-36V', 'TERM', {'1': 'GND', '2': 'VIN_RAW'}, 'WJ500V-5.08-2P', 'Kangnex', 'Input screw terminal 5.08 mm, 18 A, wire entry at the board edge (+ / - on the silkscreen)', B)
part('F1', '15A 65V', 'FUSE', {'1': 'VIN_RAW', '2': 'VIN_F'}, '0451015.MRL', 'Littelfuse', 'Last-resort input fuse (only blows if a MOSFET fails short)', B)
part('D1', 'SMBJ60CA', 'SMB', {'1': 'VIN_F', '2': 'GND'}, 'SMBJ60CA', 'Littelfuse', 'Bidirectional TVS: clamps fast spikes, silent up to 60 V DC either polarity (clamp 96.8 V < 100 V FETs)', B)
part('R1', '1R', 'R1206', {'1': 'VIN_F', '2': 'SNUB'}, '', '', 'Snubber damping resistor (kills cable-LC ringing at hot-plug)', B)
part('C1', '2.2uF 100V X7R', 'C1210', {'1': 'SNUB', '2': 'GND'}, '', '', 'Snubber capacitor', B)
part('C2', '100nF 100V X7R', 'C0603', {'1': 'VIN_F', '2': 'GND'}, '', '', 'LM74930 input bypass (datasheet min 0.1 uF)', B)
part('Q1', 'CSD19532Q5B', 'SON5x6', {'1': 'CSRC', '2': 'CSRC', '3': 'CSRC', '4': 'HGATE', '5': 'VIN_F'},
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part('R12', '5.6k', 'R1206', {'1': 'RIN2', '2': 'AIN'}, '', '', 'RED IN current limit', B)
part('D5', 'BAS21', 'SOT23', {'1': 'GND', '3': 'A1'}, 'BAS21', '', 'RED IN: reverse-polarity path from GND', B)
part('LED2', 'RED  IN', 'LED0805', {'2': 'AIN', '1': 'KIN'}, '', '', 'Input fault / reversed input indicator', B)
part('D6', 'BAS21', 'SOT23', {'1': 'KIN', '3': 'FLT'}, 'BAS21', '', 'Protects FLT pin from negative voltage', B)
part('D7', 'BAS21', 'SOT23', {'1': 'KIN', '3': 'VIN_F'}, 'BAS21', '', 'RED IN: reverse path into negative VIN', B)

# =====================================================================================
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for ref in ['C12', 'C13', 'C14', 'C36']:
    part(ref, '10uF 100V X7S', 'C1210', {'1': 'VOUT_C', '2': 'GND'}, 'GRM32EC72A106KE05L', 'Murata', 'COUT ceramic (hot loop 2) — bridges Q6 drain and Q5 source directly', B)
part('C18', '47uF 50V hybrid', 'CP8', {'1': 'VOUT_C', '2': 'GND'}, 'EEHZA1H470P', 'Panasonic', 'COUT bulk hybrid polymer 8x10, ESR 30 mOhm, 1.8 A ripple @105 C, 10,000 h', B)
part('C19', '1uF 100V X7R', 'C0805', {'1': 'VIN_P', '2': 'GND'}, '', '', 'LT8390 VIN pin bypass (close to pin 7)', B)
part('R45', '100R', 'R0603', {'1': 'VOUT_C', '2': 'VOUT_U1'}, '', '', 'VOUT pin RC filter + current limit: <4 mA into pin 24 even if VOUT_C goes negative (pin draws <60 uA)', B)
part('C20', '1uF 100V X7R', 'C0805', {'1': 'VOUT_U1', '2': 'GND'}, '', '', 'LT8390 VOUT pin bypass / RC filter (tau 10 us)', B)
part('C21', '10uF 16V X7R', 'C0805', {'1': 'INTVCC', '2': 'GND'}, '', '', 'INTVCC (datasheet min 4.7 uF; 10 uF X7R keeps >4.7 uF at 5 V and works to 125 C)', B)
part('C22', '1uF 16V X7R', 'C0603', {'1': 'INTVCC', '2': 'GND'}, '', '', 'Extra INTVCC decoupling at the pin', B)
part('C23', '470nF 16V X7R', 'C0603', {'1': 'VREF', '2': 'GND'}, '', '', 'VREF bypass (datasheet 0.47 uF)', B)
part('C24', '1uF 16V X7R', 'C0603', {'1': 'BST1', '2': 'SW1'}, '', '', 'Bootstrap cap A (>=100x Qg), right at U1 pins 2-3', B)
part('C25', '1uF 16V X7R', 'C0603', {'1': 'BST2', '2': 'SW2'}, '', '', 'Bootstrap cap D, right at U1 pins 26-27', B)
part('R20', '140k 1%', 'R0603', {'1': 'RT', '2': 'GND'}, '', '', 'RT: 300 kHz (datasheet table 1)', B)
part('C28', '220nF 16V X7R', 'C0603', {'1': 'SS', '2': 'GND'}, '', '', 'Soft-start (10x VC cap)', B)
part('R21', '100k 1%', 'R0603', {'1': 'SS', '2': 'VREF'}, '', '', 'SS->VREF 100k = keep-running mode (CC into a short)', B)
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part('R24', '46.4k 1%', 'R0603', {'1': 'EN', '2': 'GND'}, '', '', 'EN/UVLO bottom', B)
part('RV1', '200k CV', 'POT', {'1': 'VOUT_C', '2': 'FBD', '3': 'FBD'}, '3296W-1-204', 'Bourns', 'CV adjust (25-turn): VOUT = 1 V x (RV1+R25)/R25 -> 1.6-39 V (>=35.4 V with a -10 % pot)', B)
part('R25', '5.23k 1%', 'R0603', {'1': 'FBD', '2': 'GND'}, '', '', 'FB divider bottom resistor', B)
part('R46', '10k', 'R0603', {'1': 'FBD', '2': 'FB'}, '', '', 'FB pin series resistor: limits current when a battery above 6x the CV setting back-drives the divider', B)
part('D14', 'MM3Z5V1', 'SOD323', {'1': 'FB', '2': 'GND'}, 'MM3Z5V1T1G', 'onsemi', 'Clamps FB pin below its 6 V abs max (with R46)', B)
part('C33', '47pF C0G', 'C0603', {'1': 'FB', '2': 'GND'}, '', '', 'FB noise filter at the pin (pole ~600 kHz, no loop impact)', B)
part('TH1', 'PRF18BC471', 'R0603', {'1': 'VREF', '2': 'CTRLP'}, 'PRF18BC471QB5RB', 'Murata', 'PTC: 470R cold, 4.7k@105C, 47k@120C -> thermal foldback/shutdown', B)
part('R26', '20k 1%', 'R0603', {'1': 'CTRLP', '2': 'CTRL'}, '', '', 'CTRL divider top', B)
part('RV2', '50k CC', 'POT', {'1': 'CTRL', '2': 'CTRLB', '3': 'CTRLB'}, '3296W-1-503', 'Bourns', 'CC adjust (25-turn): 0.94-8.3 A', B)
part('R27', '4.53k 1%', 'R0603', {'1': 'CTRLB', '2': 'GND'}, '', '', 'CTRL divider bottom (sets CTRL min 0.362 V > 0.34 V latch)', B)
part('C34', '10nF X7R', 'C0603', {'1': 'CTRL', '2': 'GND'}, '', '', 'CTRL noise filter at the pin', B)
part('R28', '10R', 'R0603', {'1': 'ISP_K', '2': 'ISP_R'}, '', '', 'ISP series (protects pin during faults)', B)
part('R29', '10R', 'R0603', {'1': 'ISN_K', '2': 'ISN_R'}, '', '', 'ISN series', B)
part('D8', '1N4148WS', 'SOD323', {'2': 'ISP_R', '1': 'ISN_R'}, '1N4148WS', '', 'Clamp ISP-ISN < 1 V abs max', B)
part('D9', '1N4148WS', 'SOD323', {'2': 'ISN_R', '1': 'ISP_R'}, '1N4148WS', '', 'Clamp (other direction)', B)
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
